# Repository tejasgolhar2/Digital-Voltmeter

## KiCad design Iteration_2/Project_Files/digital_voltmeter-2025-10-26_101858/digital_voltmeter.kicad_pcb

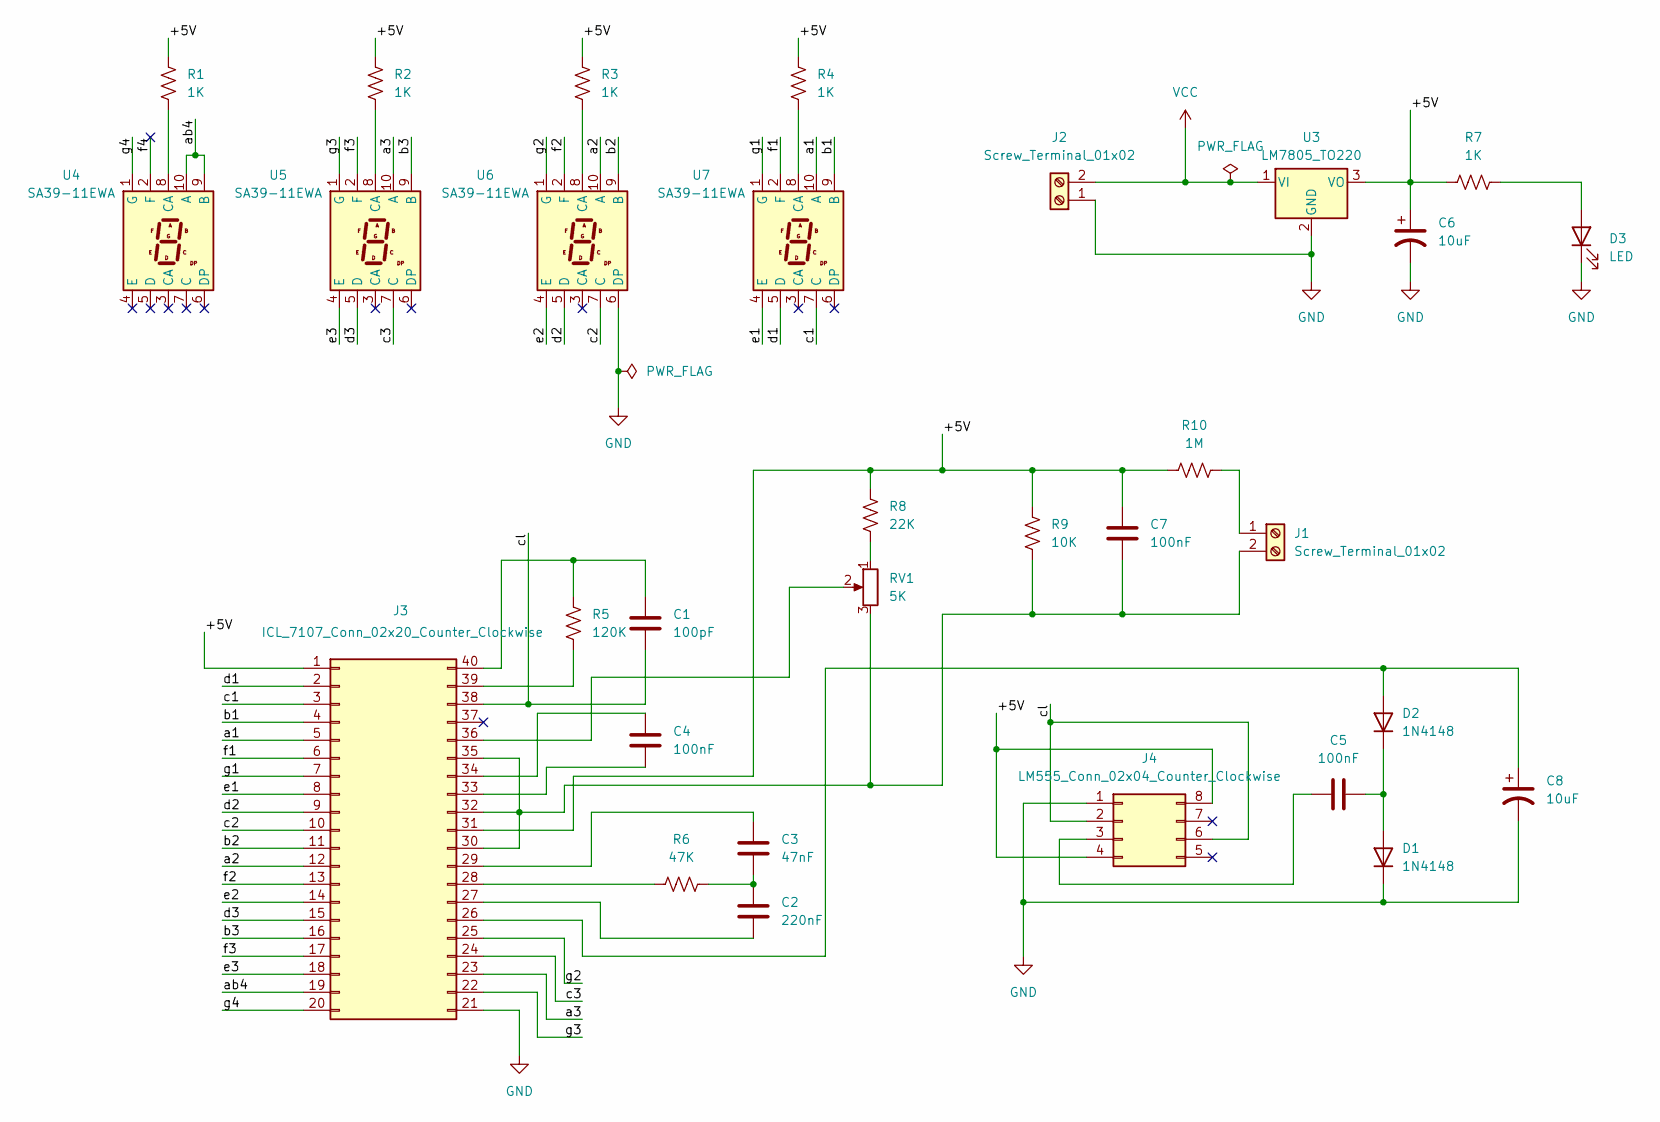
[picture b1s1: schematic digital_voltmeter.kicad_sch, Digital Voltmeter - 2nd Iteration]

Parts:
C1: 100pF; C_Disc_D3.0mm_W1.6mm_P2.50mm
C2: 220nF; C_Disc_D3.0mm_W1.6mm_P2.50mm
C3: 47nF; C_Disc_D3.0mm_W1.6mm_P2.50mm
C4, C5, C7: 100nF; C_Disc_D3.0mm_W1.6mm_P2.50mm
C6, C8: 10uF; CP_Radial_D6.3mm_P2.50mm
D1, D2: 1N4148; D_DO-35_SOD27_P7.62mm_Horizontal
D3: LED; LED_D5.0mm
J1, J2: Screw_Terminal_01x02; TerminalBlock_Phoenix_MKDS-1,5-2_1x02_P5.00mm_Horizontal
J3: ICL_7107_Conn_02x20_Counter_Clockwise; DIP-40_W15.24mm
J4: LM555_Conn_02x04_Counter_Clockwise; DIP-8_W7.62mm
R1, R2, R3, R4, R7: 1K; R_Axial_DIN0207_L6.3mm_D2.5mm_P7.62mm_Horizontal
R5: 120K; R_Axial_DIN0207_L6.3mm_D2.5mm_P7.62mm_Horizontal
R6: 47K; R_Axial_DIN0207_L6.3mm_D2.5mm_P7.62mm_Horizontal
R8: 22K; R_Axial_DIN0207_L6.3mm_D2.5mm_P7.62mm_Horizontal
R9: 10K; R_Axial_DIN0207_L6.3mm_D2.5mm_P7.62mm_Horizontal
R10: 1M; R_Axial_DIN0207_L6.3mm_D2.5mm_P7.62mm_Horizontal
RV1: 5K; Potentiometer_Bourns_3386P_Vertical
U3: LM7805_TO220; TO-220-3_Vertical
U4, U5, U6, U7: SA39-11EWA; Sx39-1xxxxx

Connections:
/+5V: C6.1, C7.1, J3.1, J3.31, J4.4, J4.8, R1.1, R2.1, R3.1, R4.1, R7.1, R8.1, R9.1, R10.1, U3.3 (VO)
/a1: J3.5, U7.10 (A)
/a2: J3.12, U6.10 (A)
/a3: J3.23, U5.10 (A)
/ab4: J3.19, U4.9 (B), U4.10 (A)
/b1: J3.4, U7.9 (B)
/b2: J3.11, U6.9 (B)
/b3: J3.16, U5.9 (B)
/c1: J3.3, U7.7 (C)
/c2: J3.10, U6.7 (C)
/c3: J3.24, U5.7 (C)
/cl: C1.2, J3.38, J4.2, J4.6
/d1: J3.2, U7.5 (D)
/d2: J3.9, U6.5 (D)
/d3: J3.15, U5.5 (D)
/e1: J3.8, U7.4 (E)
/e2: J3.14, U6.4 (E)
/e3: J3.18, U5.4 (E)
/f1: J3.6, U7.2 (F)
/f2: J3.13, U6.2 (F)
/f3: J3.17, U5.2 (F)
/f4: U4.2 (F)
/g1: J3.7, U7.1 (G)
/g2: J3.25, U6.1 (G)
/g3: J3.22, U5.1 (G)
/g4: J3.20, U4.1 (G)
GND: C6.2, C8.2, D1.1 (K), D3.1 (K), J2.1, J3.21, J4.1, U3.2 (GND), U6.6 (DP)
unnamed: C2.1, C3.1, R6.1
unnamed: C5.2, D1.2 (A), D2.1 (K)
unnamed: C8.1, D2.2 (A), J3.26
unnamed: D3.2 (A), R7.2
unnamed: J1.1, R10.2
unnamed: C7.2, J1.2, J3.30, J3.32, J3.35, R9.2, RV1.3
unnamed: C2.2, J3.27
unnamed: J3.28, R6.2
unnamed: C3.2, J3.29
unnamed: C4.1, J3.33
unnamed: C4.2, J3.34
unnamed: J3.36, RV1.2
unnamed: J3.39, R5.2
unnamed: C1.1, J3.40, R5.1
unnamed: C5.1, J4.3
unnamed: R1.2, U4.8 (CA)
unnamed: R2.2, U5.8 (CA)
unnamed: R3.2, U6.8 (CA)
unnamed: R4.2, U7.8 (CA)
unnamed: R8.2, RV1.1
VCC: J2.2, U3.1 (VI)

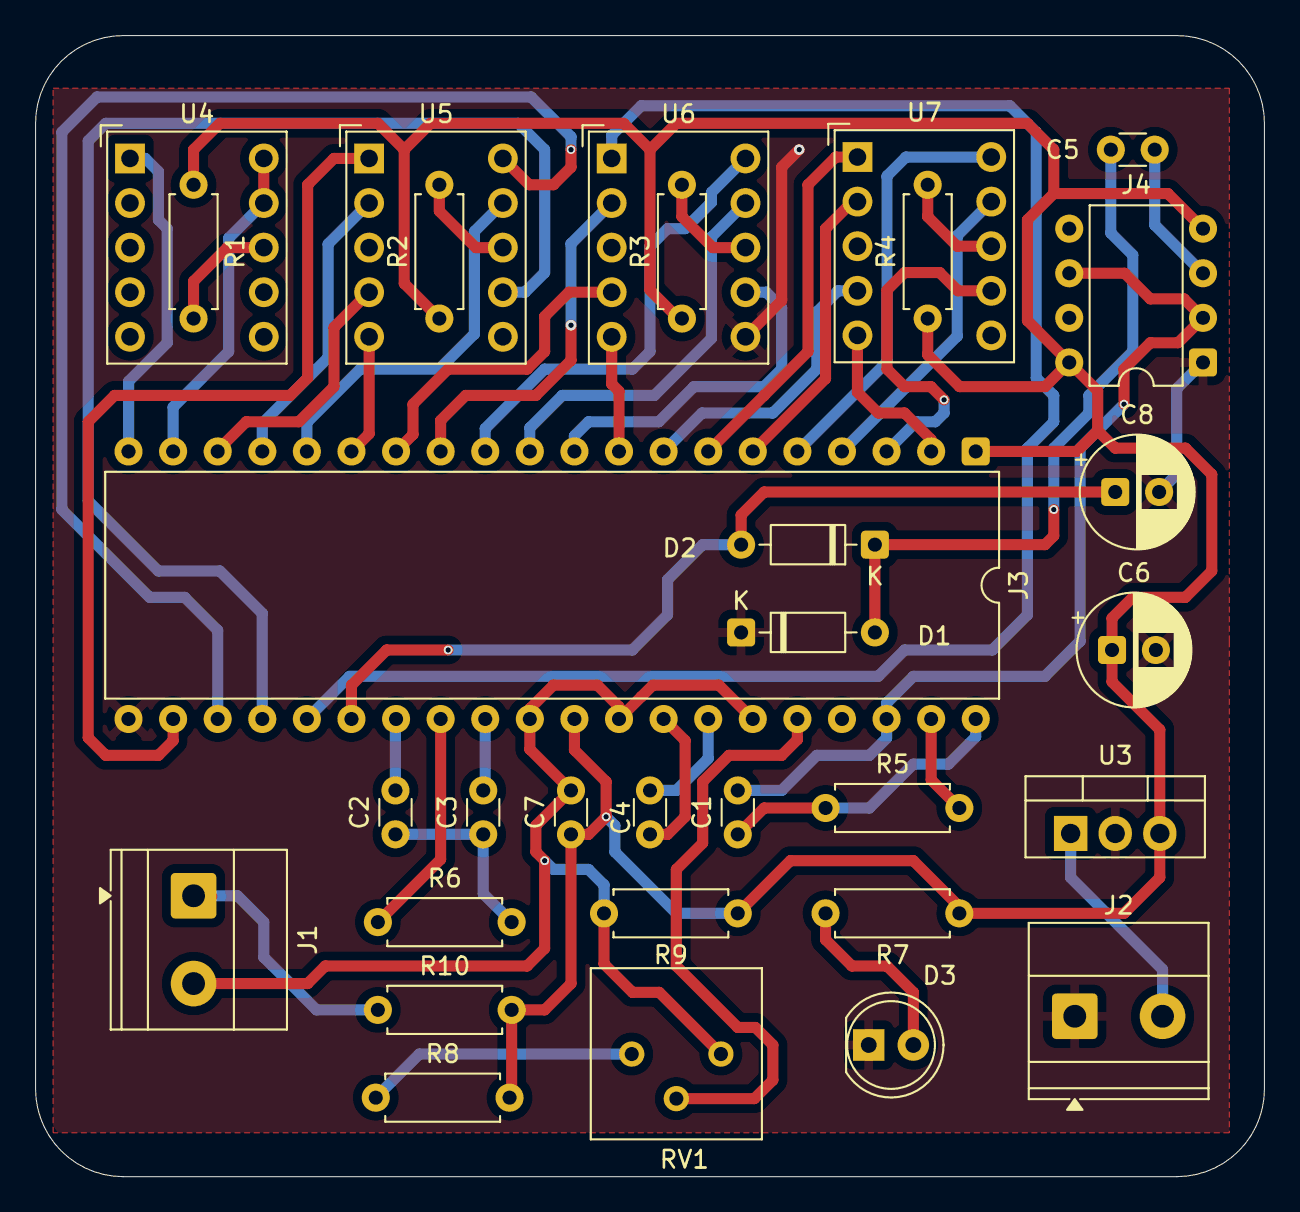
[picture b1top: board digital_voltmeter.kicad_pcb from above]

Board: 2 copper layers, 70.0 x 65.0 mm, 31 parts (0 on the bottom side), 47 nets.

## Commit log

2023-10-16 Data Sheet for ICL 7107 ADC
2023-10-16 LM555 Timer IC Datasheet
2023-10-19 Block Diagram Explanation for Simple Digital Voltmeter
2025-10-19 schematic_image
